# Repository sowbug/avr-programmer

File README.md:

AVR In-System Programmer
========================

By [Mike Tsao](http://www.sowbug.com/) and [Dennis Gentry](https://github.com/dgentry)

Introduction
============

This is a new spin on the AVR ISP. It's based on the ATmega 'u2 family of AVR devices. Influences while designing, in no particular order:

  * Adafruit's [USBtinyISP](http://www.ladyada.net/make/usbtinyisp/), based on [the original USBtiny project](http://dicks.home.xs4all.nl/avr/usbtiny/). In particular, the buffer came from this project.
  * Fabio Baltieri's [USB Key AVR Programmer](http://fabiobaltieri.com/2011/09/02/usb-key-avr-programmer/). Some early schematic ideas came from here.
  * [Saleae Logic](http://www.saleae.com/logic). Yes, I know that's not an AVR programmer, but I like their design sensibilities.
  * [Frank Zhao](http://frank-zhao.com/) provided feedback on an early version of the circuit.

Design Goals
============

  1. It should be pocketable, or capable of being kept in a mesh backpack compartment, without snagging on anything. This means SMD rather than through-hole, few or no required pin headers, and right-angle headers where headers are required.
  1. No special cables needed. In the common case of a standard 6-pin ISP header on the target board, the programmer needs only a commodity mini-B USB cable. The target audience is DIY people who are designing their own circuits, and in that case it's very unlikely new designs would use a 10-pin ISP header with 4 NC pins.
  1. It should be a real USB device rather than emulating serial over USB, so it needs fewer avrdude options to pass in.
  1. Jumpers should be truly optional. The device should be usable without jumper header pins even soldered onto the board.
  1. Support in current versions of avrdude. With the real-USB-device requirement, this narrows it down to USBasp, USBtiny, or AVRISP mkII emulation.
  1. Inexpensive. To be clear, most AVR programmers are inexpensive, and it's not a goal to be less expensive than them.
  1. Distinctive. The angled 6-pin socket satisfies this goal.
  1. Fast. This should be entirely dependent on the quality of the firmware, because the device itself should be capable of high-speed USB.
  1. Good-looking enough to be presentable without a case.
  1. JTAG/XSVF programming via [The JTAG Whisperer](https://github.com/sowbug/JTAGWhisperer). This means we need to support varying target voltages.
  1. Bring out the serial pins on the ATmega to provide a USB-to-TTL converter with an FTDI-cable-compatible pinout.
  1. Support for all low-voltage programming methods (SPI, TPI, PDI). Note that TPI/PDI turned out to be hard to do with the serial functionality. It should work, but with external resistors and a breadboard.

Notes That Will Someday Become Documentation
============================================

* Fuses are **-U lfuse:w:0xDE:m -U hfuse:w:0xD9:m -U efuse:w:0xF7:m -U lock:w:0xFF:m**. These are default with 16MHz crystal and HWBE=0.

FAQ
===

  * **Err, USBasp? USBtiny? You know those bitbang USB, right? Why consider those protocols if your ATmegaXXu2 has native USB?** It's just a question of avrdude support. Both those protocols are based on open-source hardware, so I'd prefer to base my work on them. Another consideration is that there shouldn't be a problem with borrowing their VID/PID pairs. The bit-banging aspect of the protocols is orthogonal to their suitability.
  * **Your circuit mentions the ATmega8u2. You know the '32u2 is only like $1.00 more, right?** True (actually only 40 cents more in quantity), and the initial prototypes will use the '32u2. But we're going to try to fit the intended functionality into 8KB flash and 512 bytes SRAM. Beyond that, the device is looking more like a general-purpose gadget. If we were building such a thing, the ATmega32u4 (not the 32u2) is a better choice.
  * **About that general-purpose gadget: why aren't you building one? The [Bus Pirate](http://dangerousprototypes.com/docs/Bus_Pirate) is cool.** Yes, the Bus Pirate is cool, and indeed it would be nice to have one built on an open toolchain. But this isn't that device. The intent is to have a specialized tool that's always available, never needing a misplaced cable, never needing a firmware update, during those times when you've bricked an AVR or CPLD and just need it fixed.
  * **What's this about AVRISP mkII?** Right, at the moment the prototypes are running the [LUFA project AVRISP mkII](http://www.fourwalledcubicle.com/AVRISP.php). This hardware doesn't include any of its own software, but just in case you build a copy and run LUFA on it, we'd like to incorporate [LUFA's MIT-style license](https://github.com/sowbug/lufa-lib/blob/master/trunk/LUFA/License.txt) and [copyright notice](https://github.com/sowbug/lufa-lib/blob/master/trunk/LUFA/Version.h) by reference here. Thanks, Dean!

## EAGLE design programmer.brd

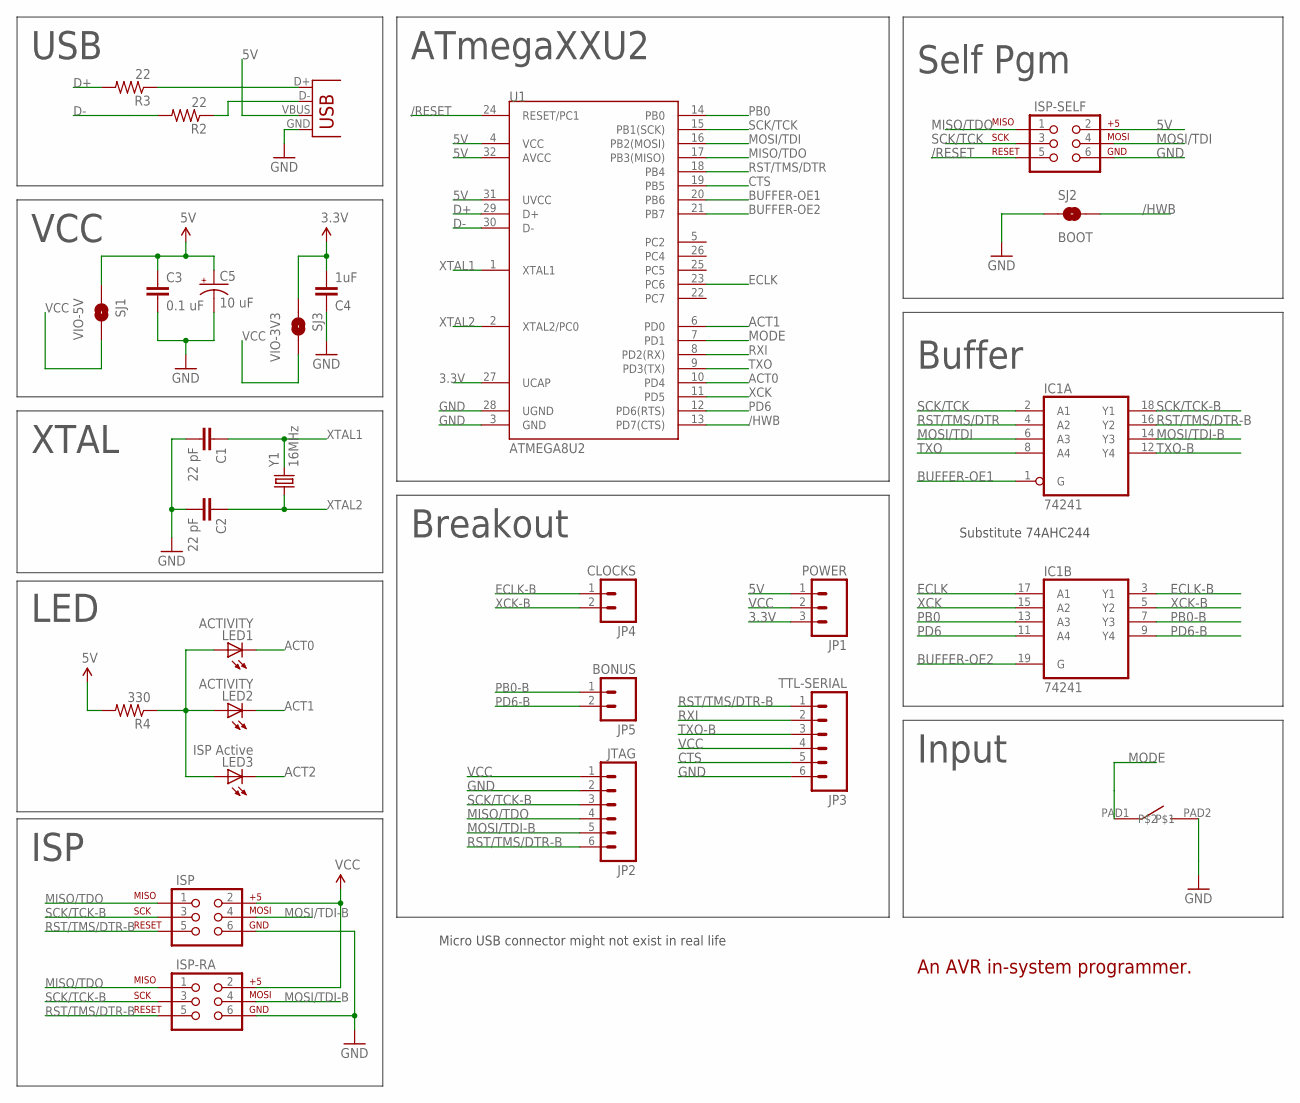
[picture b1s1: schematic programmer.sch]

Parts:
C1, C2: 22 pF; SPARKFUN_0805
C3: 0.1 uF; SPARKFUN_0805
C4: 1uF; SPARKFUN_0805
C5: 10 uF; SPARKFUN_EIA3216
IC1: 74241; TSSOP20
ISP: SPARKFUN_AVR_SPI_PRG_62X3_LOCK; SPARKFUN_2X3_LOCK
ISP-RA: SPARKFUN_AVR_SPI_PRG_62X3_LOCK; SPARKFUN_2X3_LOCK
ISP-SELF: SPARKFUN_AVR_SPI_PRG_62X3_LOCK; SPARKFUN_2X3_LOCK
JP1: POWER; SPARKFUN_1X03_LOCK
JP2: JTAG; SPARKFUN_1X06_LOCK
JP3: TTL-SERIAL; SPARKFUN_1X06_LOCK
JP4: CLOCKS; 1X02_LOCK
JP5: BONUS; 1X02_LOCK
LED1, LED2: ACTIVITY; CHIP-LED0805
LED3: ISP Active; CHIP-LED0805
R2, R3: 22; SPARKFUN_0805
R4: 330; SPARKFUN_0805
SJ1: VIO-5V; SPARKFUN_SJ_2S
SJ2: BOOT; SPARKFUN_SJ_2S-NO
SJ3: VIO-3V3; SPARKFUN_SJ_2S
SW1: BUTTON_TD-85XU
U1: ATMEGA8U2; SPARKFUN_TQFP32-08
X1: FCI_8193_MICRO_USB; FCI_MICRO_USB_8193
Y1: 16MHz; SPARKFUN_CRYSTAL-SMD-5X3

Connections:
3.3V: C4.2, JP1.3, SJ3.1, U1.27 (UCAP)
5V: C3.1, C5.A (+), ISP-SELF.2, JP1.1, R4.2, SJ1.1, U1.4 (VCC), U1.31 (UVCC), U1.32 (AVCC), X1.VBUS
/HWB: SJ2.2, U1.13 (PD7(CTS))
/RESET: ISP-SELF.5, U1.24 (RESET/PC1)
ACT0: LED1.C, U1.10 (PD4)
ACT1: LED2.C, U1.6 (PD0)
ACT2: LED3.C
BUFFER-OE1: IC1.1 (G), U1.20 (PB6)
BUFFER-OE2: IC1.19 (G), U1.21 (PB7)
CTS: JP3.5, U1.19 (PB5)
D+: R3.2, U1.29 (D+)
D+RAW: R3.1, X1.D+
D-: R2.2, U1.30 (D-)
D-RAW: R2.1, X1.D-
ECLK: IC1.17 (A1), U1.23 (PC6)
ECLK-B: IC1.3 (Y1), JP4.1
GND: C1.2, C2.2, C3.2, C4.1, C5.C (-), IC1.10 (GND), ISP.6, ISP-RA.6, ISP-SELF.6, JP2.2, JP3.6, SJ2.1, SW1.PAD2, U1.3 (GND), U1.28 (UGND), X1.GND
MISO/TDO: ISP.1, ISP-RA.1, ISP-SELF.1, JP2.4, U1.17 (PB3(MISO))
MODE: SW1.PAD1, U1.7 (PD1)
MOSI/TDI: IC1.6 (A3), ISP-SELF.4, U1.16 (PB2(MOSI))
MOSI/TDI-B: IC1.14 (Y3), ISP.4, ISP-RA.4, JP2.5
PB0: IC1.13 (A3), U1.14 (PB0)
PB0-B: IC1.7 (Y3), JP5.1
PD6: IC1.11 (A4), U1.12 (PD6(RTS))
PD6-B: IC1.9 (Y4), JP5.2
RST/TMS/DTR: IC1.4 (A2), U1.18 (PB4)
RST/TMS/DTR-B: IC1.16 (Y2), ISP.5, ISP-RA.5, JP2.6, JP3.1
RXI: JP3.2, U1.8 (PD2(RX))
SCK/TCK: IC1.2 (A1), ISP-SELF.3, U1.15 (PB1(SCK))
SCK/TCK-B: IC1.18 (Y1), ISP.3, ISP-RA.3, JP2.3
TXO: IC1.8 (A4), U1.9 (PD3(TX))
TXO-B: IC1.12 (Y4), JP3.3
VCC: IC1.20 (VCC), ISP.2, ISP-RA.2, JP1.2, JP2.1, JP3.4, SJ1.2, SJ3.2
VCC-LED: LED1.A, LED2.A, R4.1
VCC-LED1: LED3.A
XCK: IC1.15 (A2), U1.11 (PD5)
XCK-B: IC1.5 (Y2), JP4.2
XTAL1: C1.1, U1.1 (XTAL1), Y1.3 (2)
XTAL2: C2.1, U1.2 (XTAL2/PC0), Y1.1

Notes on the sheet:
USB
ISP
Self Pgm
VCC
XTAL
LED
An AVR in-system programmer.
Buffer
Breakout
ATmegaXXU2
Micro USB connector might not exist in real life
Substitute 74AHC244
Input

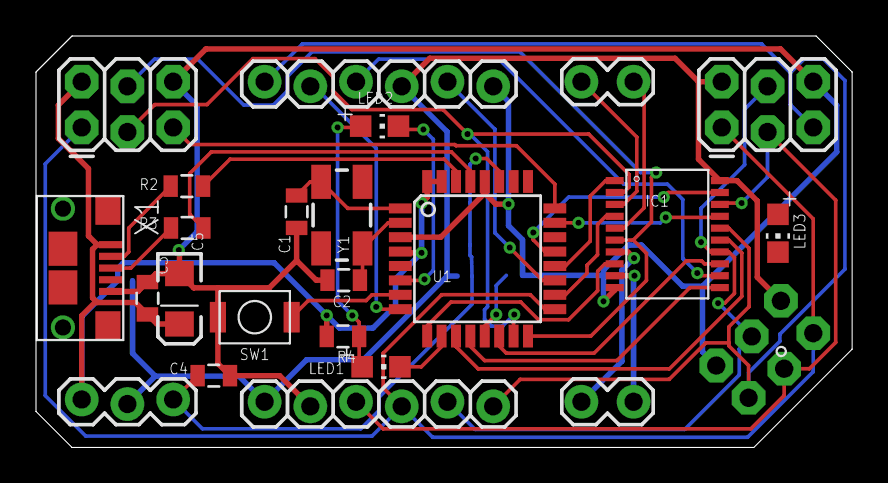
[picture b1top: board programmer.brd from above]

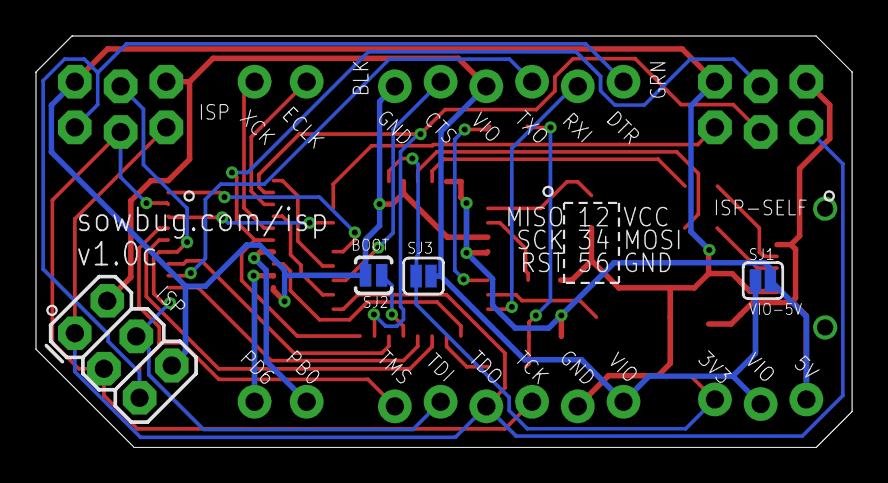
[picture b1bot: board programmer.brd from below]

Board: 2 copper layers, 45.3 x 22.9 mm, 27 parts (4 on the bottom side), 37 nets.

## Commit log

2012-02-25 New. Notched design.
2012-02-25 Angled 6-pin ISP.
2012-02-25 Blinkenlights.
2012-02-25 More work on layout. SJ1. Polarized 10uF cap. Fixed ISP2 orientation.
2012-02-25 Generated schematic image.
2012-02-25 Wider. Added SJ1 connection.
2012-02-25 Better routing setup. Moved SJ1 jumper temporarily.
2012-02-25 New.
2012-02-25 Improve text and formatting.
2012-02-25 Nudge here and there to get rid of DRC errors.
2012-02-26 Fixed error in self-program jumper. Balanced components.
2012-02-26 Removed BUFF-OE.
2012-02-26 Added buffer and JTAG/voltage pinouts.
2012-02-26 Fixed '125 name on board.
2012-02-26 Named all netlists. More consistent lettering.
2012-02-26 Pour ground planes.
2012-02-27 Fixed resistor numbering. Moved SJ1 jumper off board. Won't autoroute.
2012-02-27 Got it to route by adding polygons afterward.
2012-02-27 .gitignore
2012-02-27 Updated.
2012-02-27 VCC is now independent of uC supply. Thx Frank Zhao!
2012-02-28 Smaller, fewer vias
2012-02-28 Resolved conflicts with dgentry's optimizations.
2012-02-28 Ground planes.
2012-02-28 Fixed: PB0 replaced with RST for JTAG header.
2012-02-28 Fixed miswired RESET/RST/RST-UC.
2012-03-03 v1.0.1, 1 via
2012-03-03 v1.0s. s for squished
2012-03-03 Moved ISP6 dot. Removed floating jumper connector.
2012-03-03 README update.
2012-03-03 Improved power and GND polygons, moved sowbug.com to a place where it won't get drilled
2012-03-03 Beefed up GND on bottom layer; cleaned up messy thermal/routing interaction near uC power
2012-03-20 Made labels bigger, where possible.
2012-03-20 Added pictures of the top and bottom. A script or ULP or CAM job to generate these would be even better.
2012-03-25 Everything is messed up.
2012-03-26 Rearranged a bit, routed. 9 vias. Could do better with some pinswapping.
2012-03-27 Can't take the checkpoint cruft any more
2012-04-01 Fixed labels. Nothing is obscured.
2012-04-01 Removed unnecessary pullups. Moved bottom labels to right layer.
2012-04-01 Ground planes were nothing planes. Fixed.
2012-04-01 Cleanup.
2012-04-01 Moved all parts to local lbr. IC2->IC1.
2012-04-01 zipfile to be sent to Laen.
2012-04-01 Renamed to match version number on silkscreen.
2012-04-03 Re-route to 24 vias.
2012-04-03 Added ground planes and some ground vias
2012-04-03 Got rid of obsolete .pngs. Also, this routing uses fat power and ground.
2012-04-03 Pass design rules and write a .png
2012-04-03 Shrunk a bit.
2012-04-03 Nudged vias off bottom silk text.
2012-04-03 Rename, regenerate.
2012-04-03 Removed old png.
2012-04-04 Aligned labels. Isolated 6-pin JTAG and TTL-serial headers.
2012-04-04 An unknown change after pouring the ground planes.
2012-04-04 index on master: def4ad0 Can't take the checkpoint cruft any more
2012-04-04 Added gratuitous ground plane vias for more complete coverage. There was already one (routing, not ground plane) via in a slightly bottom silk-obscuring place, but this change doesn't add any more.
2012-04-04 Passes design rules now. More gratuitous ground plane vias, none of which obscure silk.
2012-04-04 It occurs to me that we might have different design rules, so checking these in. Not positive these are the latest Laen ones, but I'll go check and update if not.
2012-04-04 Fresh re-route. 18 vias.
2012-04-04 11 vias and smaller. Routing is circuitous, but hey, it's a circuit.
2012-04-04 Reasonable routing, smaller, still 11 vias. Is it buildable?
2012-04-04 Passes all DRC/ERC, few overlaps. Smaller board, fewer vias (except groundplane ones, which are numerous). Maybe 11 or 13.
2012-04-04 And a board .png
2012-04-05 Redid .png at 300 dpi for easier comparison with prior version in github's cool image comparison tools.
2012-04-11 8 mil traces and vias = cheaper fab
2012-04-12 8 mil, reasonable routing.
2012-04-12 DP_exporter initial checkin. Probably doesn't work.
2012-04-12 8 mil traces, 14 vias, beveled corners
2012-04-12 PNG for new, cheaper layout
2012-04-12 Add note about substituting '244.
2012-04-12 Untabify, 2 char indents. Sorry, couldn't take the 8 char/tab indents.
2012-04-12 Modified for Unix filenames. Use the old version if you are running DOS.
2012-04-12 And here's the .sch it wrote.
2012-04-12 DP's auto-generated BOM, in inconvenient HTML format\!
2012-04-20 Prebuilt hex for alpha hardware.
2012-04-24 Renamed old, added new.
2012-04-24 Documentation about fuses.
2012-04-24 Whoops, didn't really add. Fixed.
2012-04-26 Various changes.
    - Change VCC labels to VIO (https://github.com/sowbug/avr-programmer/issues/15).
    - Change LED resistor from 1K to 330 (https://github.com/sowbug/avr-programmer/issues/16).
    - Added second status LED (https://github.com/sowbug/avr-programmer/issues/9).
2012-04-26 Add SJ3 for 3V3 -> VIO.
2012-04-27 Added switch.
2012-04-28 Add FCI 10118193 USB socket.
2012-04-28 Adjust pads.
2012-04-28 Switched drill to via, so we get a bit of solder mask around the pegs.
2012-04-28 Switch to funky TD-85XU button.
2012-04-29 Switch and LED at East End -- probably not ideal
2012-04-29 Add a few links to LUFA.
2012-04-30 Switch up by the USB, LED still by the ISP header. Just a checkpoint, not a fab candidate.
2012-04-30 v1.1, vias out of the way of bottom silk, still need to move solder jumpers to more pleasing locations.
2012-05-09 Datasheets.
2012-05-09 Move .hex into firmware/.
2012-05-23 3 Activity LEDs. One might not be hooked up yet, though.

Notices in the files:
parts and their libraries:
SparkFun: Licensing: CC v3.0 Share-Alike You are welcome to use this library for commercial purposes.
